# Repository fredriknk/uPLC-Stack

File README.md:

# uPLC - Miniaturized Distributed Monitoring and Control

Quick note, this is then panelization repo, head for the individual repos to get design files.

### PcbWay Sponsorship

Thanks so much to [PCBWay](https://www.pcbway.com/) for sponsoring my first assembly run for this project, they deliver awesome quality assembly service as always with 6 perfectly soldered dual sided prototypes delivered at my door in less than 2 weeks from ordering. All components perfectly placed and good quality 4 layer pcb's. I love the look and legebility of the 0.9mm inverted silkscreen texts. They even pointed out some reccomended component replacements due to NRND bom items. So Look at this beautiful trio of boards ready for automating every dumb device in my house. 

ESP-Home code examples are comming soon.

The uPLC (micro Programmable Logic Controller) is a compact (22x32mm) I/O controller powered by the ESP32, designed to automate various tasks around you. So far, three versions have been developed. All versions are generally 24V-tolerant for digital I/O, except for the analog inputs, and feature a wide-range 3.8-24V buck regulator for power input.

The primary purpose of the uPLC is to "smartify" devices by integrating them with [ESPHome](https://esphome.io/). But it can also function as a direct, point-to-point PLC, using **ESP-NOW** for wireless communication, replacing traditional wired connections at a cost of latency. 

## Available Versions:
- **[uPLC-Digital](https://github.com/fredriknk/uPLC-digital):** High-speed digital I/O
- **[uPLC-Relay](https://github.com/fredriknk/uPLC-relay):** Relays and digital I/O
- **[uPLC-Analog](https://github.com/fredriknk/uPLC-Analog):** ADC and DAC

### Coming Soon:
- **uPLC-COMM:** For sensor connections- SPI, I2C, SDI12 support
- **uPLC-4_20:** Current loop for industrial sensors
- **uPLC-TBD:** If you have a good idea give me a message or issue 

## Specifications

| **Parameter**   | **Description**                                                     |
|-----------------|---------------------------------------------------------------------|
| **Input Voltage** | 3.8-24V                                                           |
| **Current Consumption**  | TBD: WiFi Active: ##mA, Radio Off: ##mA, Deep Sleep: ##uA  |  
| **Communication** | 2.4GHz Wi-Fi, UART (TTL level)                                    |
| **Baud Rate**    | 115200                                                             |
| **PCB Size**     | 22 x 31.1 mm                                                       |
| **PCB Material** | 1.6mm FR4, HASL lead-free, 4-layer                                 |
| **Case Size**    | X x X x X mm (TBD)                                                 |

## uPLC-Stack:
To facilitate manufacturing and development, I've created a panelized version using **KiKit** scripting. The uPLC-Stack includes two units of each version, making it easier to assemble and test multiple variants in one go. Im planning on

### Running the Panelization Script:
To use the panelization script, clone all the uPLC repositories and organize them in a directory one level back from the uPLC-Stack folder. This allows the KiKit script to automatically pull in all required files for panelizing.

### Stack Images

- **Perspective View**  

- **Top View**  

- **Side View**  

- **Bottom View**

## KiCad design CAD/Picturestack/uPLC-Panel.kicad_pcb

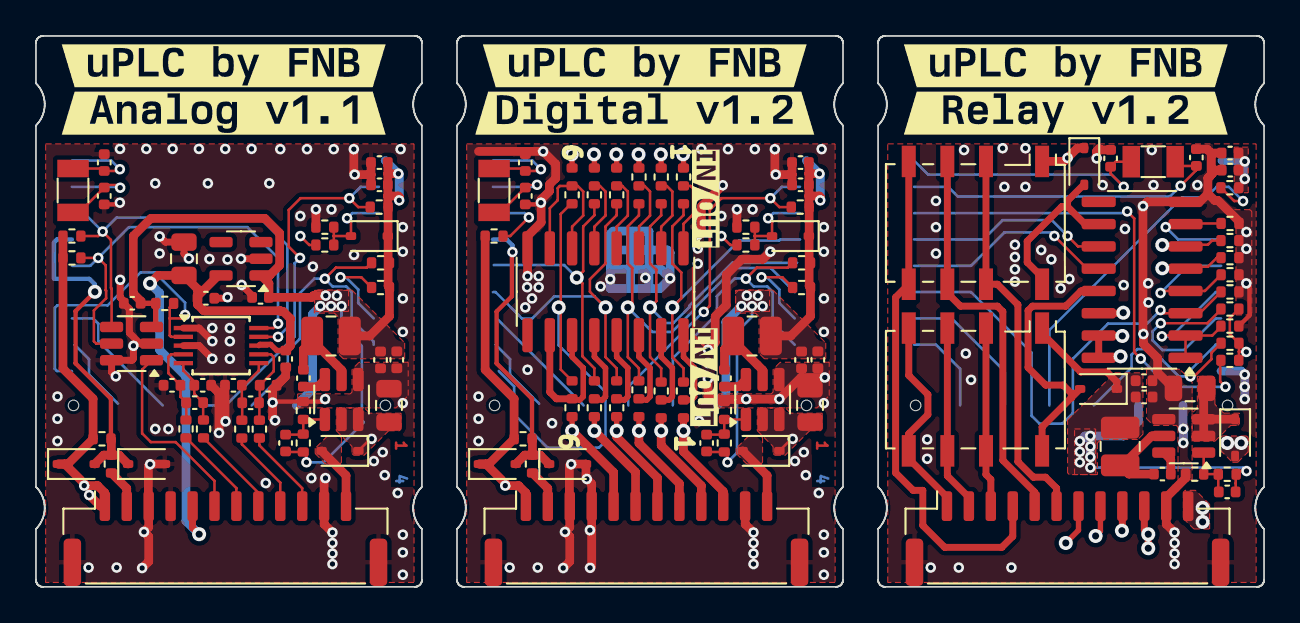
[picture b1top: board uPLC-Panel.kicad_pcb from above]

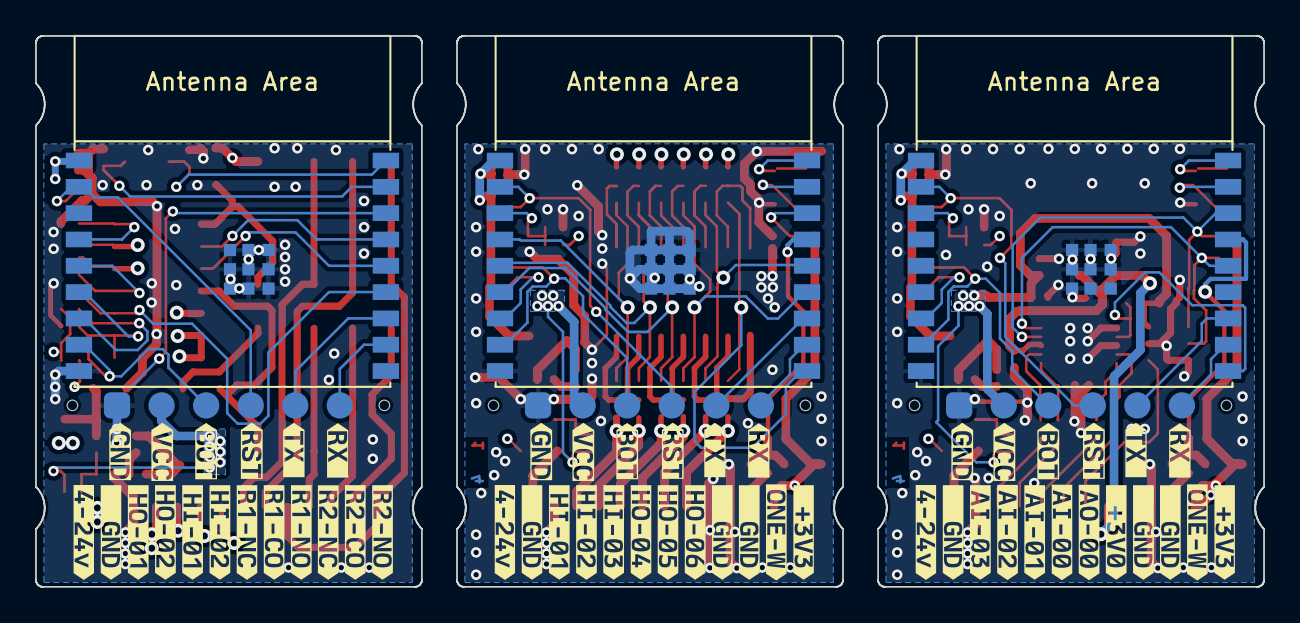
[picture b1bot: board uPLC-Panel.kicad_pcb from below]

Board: 4 copper layers, 70.0 x 31.4 mm, 186 parts (60 on the bottom side), 105 nets.

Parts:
C1.0, C1.1, C1.2, C4.0, C4.1, C4.2: 20pf; C_0402_1005Metric
C2.0, C2.1, C2.2, C3.0, C3.1, C3.2, C6.0, C9.0, C9.1, C9.2, C10.0, C13.0, C14.0, C15.0, C16.0, C17.0, C18.0, C19.0, C20.0: 0.1uF; C_0402_1005Metric
C5.0, C5.1, C5.2, C7.0: 10uF; C_0805_2012Metric
C8.0, C8.1, C8.2, C11.0, C11.1, C11.2, C12.0, C12.1, C12.2: 22uf; C_0402_1005Metric
D1.0, D1.1, D1.2, D2.0, D2.1, D2.2, D3.0, D3.1, D4.0, D4.1, D4.2: 1N5819WS; D_SOD-323
J1.0, J1.1, J1.2: Conn_01x06_Pin; TestPoint_Pad_1.0x1.0mm_6pad
J2.0, J2.1, J2.2: SM12B-GHS-TB(LF)(SN); JST_GH_SM12B-GHS-TB_1x12-1MP_P1.25mm_Horizontal
JP1.1, JP2.1, JP3.1, JP4.1, JP5.1, JP6.1, JP7.1, JP8.1, JP9.1, JP10.1, JP11.1, JP12.1: 0R; SolderJumper-3_P1.3mm_BridgedSMD12_0402
K1.2, K2.2: G6K-2F-Y; Relay_DPDT_Omron_G6K-2F-Y
L1.0, L1.1, L1.2: 4.7uH; L_1008_2520Metric
R1.0, R1.1, R1.2, R2.0, R2.1, R2.2, R3.0, R3.1, R4.0, R4.1, R4.2, R5.0, R5.1, R5.2, R6.0, R6.1, R7.2, R8.2, R9.2, R10.2, R11.2, R12.0, R12.2, R16.0: 10K; R_0402_1005Metric
R7.0, R7.1: 309k; R_0402_1005Metric
R8.0, R9.0, R10.0, R11.0: 499R; R_0402_1005Metric
R13.0, R13.1: 100R; R_0402_1005Metric
R14.0, R14.1, R14.2: 182k; R_0402_1005Metric
R15.0, R15.1, R15.2: 62k; R_0402_1005Metric
U1.0, U1.1, U1.2: AP63201WU; TSOT-23-6
U2.0: ADS1115IDGS; TSSOP-10_3x3mm_P0.5mm
U2.1, U2.2: TBD62003AFWG; SOIC-16_3.9x9.9mm_P1.27mm
U3.0, U3.1, U3.2: ESP32-C3-WROOM-02
U4.0: LP5907MFX-3.0; SOT-23-5
U5.0: MCP4725xxx-xCH; SOT-23-6
Y1.0, Y1.1, Y1.2: 32.768khz 3215 12.5pf; Crystal_SMD_3215-2Pin_3.2x1.5mm
kibuzzard-65D6FF37.2: G***; kibuzzard-65D6FF37
kibuzzard-65D8B0E2.1: G***; kibuzzard-65D8B0E2
kibuzzard-65D8B0ED.1: G***; kibuzzard-65D8B0ED
kibuzzard-65D8B0F8.1: G***; kibuzzard-65D8B0F8
kibuzzard-65D8B10C.1: G***; kibuzzard-65D8B10C
kibuzzard-65D8B28C.1: G***; kibuzzard-65D8B28C
kibuzzard-65D8B104.1: G***; kibuzzard-65D8B104
kibuzzard-65D8B121.1: G***; kibuzzard-65D8B121
kibuzzard-65D8B297.1: G***; kibuzzard-65D8B297
kibuzzard-65D8B343.1: G***; kibuzzard-65D8B343
kibuzzard-65D74DE1.0, kibuzzard-65D74DE1.0#2, kibuzzard-65D74DE1.1: G***; kibuzzard-65D74DE1
kibuzzard-65D74DEE.0, kibuzzard-65D74DEE.1: G***; kibuzzard-65D74DEE
kibuzzard-65D74DFB.0, kibuzzard-65D74DFB.1: G***; kibuzzard-65D74DFB
kibuzzard-65D361A7.2: G***; kibuzzard-65D361A7
kibuzzard-65D361B0.2: G***; kibuzzard-65D361B0
kibuzzard-65D361D3.2: G***; kibuzzard-65D361D3
kibuzzard-65D361E1.2: G***; kibuzzard-65D361E1
kibuzzard-65D361E9.2: G***; kibuzzard-65D361E9
kibuzzard-65D361F2.2: G***; kibuzzard-65D361F2
kibuzzard-65D361FD.2: G***; kibuzzard-65D361FD
kibuzzard-65D460A0.0, kibuzzard-65D460A0.1, kibuzzard-65D460A0.2: G***; kibuzzard-65D460A0
kibuzzard-65D3616E.0, kibuzzard-65D3616E.1, kibuzzard-65D3616E.2: G***; kibuzzard-65D3616E
kibuzzard-65D3619D.2: G***; kibuzzard-65D3619D
kibuzzard-65D3620E.2: G***; kibuzzard-65D3620E
kibuzzard-65D7176D.0, kibuzzard-65D7176D.1, kibuzzard-65D7176D.2: G***; kibuzzard-65D7176D
kibuzzard-65D7177B.0, kibuzzard-65D7177B.1, kibuzzard-65D7177B.2: G***; kibuzzard-65D7177B
kibuzzard-65D36177.0, kibuzzard-65D36177.1, kibuzzard-65D36177.2: G***; kibuzzard-65D36177
kibuzzard-65D36206.2: G***; kibuzzard-65D36206
kibuzzard-65D46022.0, kibuzzard-65D46022.1, kibuzzard-65D46022.2: G***; kibuzzard-65D46022
kibuzzard-65D46066.0, kibuzzard-65D46066.1, kibuzzard-65D46066.2: G***; kibuzzard-65D46066
kibuzzard-65D49092.0, kibuzzard-65D49092.1, kibuzzard-65D49092.2: G***; kibuzzard-65D49092
kibuzzard-65D71774.0, kibuzzard-65D71774.1, kibuzzard-65D71774.2: G***; kibuzzard-65D71774
kibuzzard-65DC95DA.0: G***; kibuzzard-65DC95DA
kibuzzard-65DC95E5.0: G***; kibuzzard-65DC95E5
kibuzzard-65DC95EF.0: G***; kibuzzard-65DC95EF
kibuzzard-65DC95F6.0: G***; kibuzzard-65DC95F6
kibuzzard-65DC961D.0: G***; kibuzzard-65DC961D
kibuzzard-65DC9610.0: G***; kibuzzard-65DC9610
kibuzzard-65DCA831.1: G***; kibuzzard-65DCA831
kibuzzard-65DCE4DE.0: G***; kibuzzard-65DCE4DE

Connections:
+3.3V.0: C3.0.1, C8.0.1, C9.0.1, C10.0.1, C11.0.1, C12.0.1, C14.0.1, D1.0.1 (K), D3.0.1 (K), J1.0.2, J2.0.1, L1.0.2, R1.0.1, R2.0.1, R4.0.2, R5.0.2, R6.0.1, R12.0.2, R14.0.2, R16.0.2, U3.0.1 (3V3), U4.0.1 (IN), U5.0.3 (VDD)
+3.3V.1: C3.1.1, C8.1.1, C9.1.1, C11.1.1, C12.1.1, D1.1.1 (K), D3.1.1 (K), J1.1.2, J2.1.1, L1.1.2, R1.1.1, R2.1.1, R4.1.2, R5.1.2, R6.1.1, R14.1.2, U3.1.1 (3V3)
+3.3V.2: C3.2.1, C8.2.1, C9.2.1, C11.2.1, C12.2.1, D1.2.1 (K), D2.2.1 (K), J1.2.2, K1.2.1, K2.2.1, L1.2.2, R1.2.1, R2.2.1, R4.2.2, R5.2.2, R14.2.2, U3.2.1 (3V3)
+3V0.0: C6.0.1, C7.0.1, C13.0.1, J2.0.5, U2.0.8 (VDD), U4.0.5 (OUT)
+VDC.0: D4.0.2 (A), J2.0.12
+VDC.1: D4.1.2 (A), J2.1.12
+VDC.2: D4.2.2 (A), J2.2.12
/FB.0: C9.0.2, R14.0.1, R15.0.2, U1.0.1 (FB)
/FB.1: C9.1.2, R14.1.1, R15.1.2, U1.1.1 (FB)
/FB.2: C9.2.2, R14.2.1, R15.2.2, U1.2.1 (FB)
/I1.1: JP1.1.2 (C), U2.1.1 (I1)
/I2.1: JP3.1.2 (C), U2.1.2 (I2)
/I3.1: JP5.1.2 (C), U2.1.3 (I3)
/I4.1: JP7.1.2 (C), U2.1.4 (I4)
/I5.1: JP9.1.2 (C), U2.1.5 (I5)
/I6.1: JP11.1.2 (C), U2.1.6 (I6), U2.1.7 (I7)
/O1.1: JP2.1.2 (C), U2.1.16 (O1)
/O2.1: JP4.1.2 (C), U2.1.15 (O2)
/O3.1: JP6.1.2 (C), U2.1.14 (O3)
/O4.1: JP8.1.2 (C), U2.1.13 (O4)
/O5.1: JP10.1.2 (C), U2.1.12 (O5)
/O6.1: JP12.1.2 (C), U2.1.10 (O7), U2.1.11 (O6)
/SW.0: C2.0.1, L1.0.1, U1.0.5 (SW)
/SW.1: C2.1.1, L1.1.1, U1.1.5 (SW)
/SW.2: C2.2.1, L1.2.1, U1.2.5 (SW)
/VIN_P.0: C5.0.1, D4.0.1 (K), R7.0.1, U1.0.2 (EN), U1.0.3 (IN)
/VIN_P.1: C5.1.1, D4.1.1 (K), R7.1.1, U1.1.2 (EN), U1.1.3 (IN)
/VIN_P.2: C5.2.1, D4.2.1 (K), U1.2.2 (EN), U1.2.3 (IN)
ADC.0: D3.0.2 (A), R3.0.1, R7.0.2, U3.0.3 (GPIO4/ADC1_CH4)
ADC.1: D3.1.2 (A), R3.1.1, R7.1.2, U3.1.3 (GPIO4/ADC1_CH4)
ADC_DRDY.0: R12.0.1, U2.0.2 (ALERT/RDY), U3.0.10 (GPIO10)
AIN0.0: J2.0.7, R8.0.2
AIN1.0: J2.0.8, R9.0.2
AIN2.0: J2.0.9, R10.0.2
AIN3.0: J2.0.10, R11.0.2
AOUT0.0: J2.0.6, U5.0.1 (VOUT)
BOOT.0: J1.0.3, R2.0.2, U3.0.8 (GPIO9)
BOOT.1: J1.1.3, R2.1.2, U3.1.8 (GPIO9)
BOOT.2: J1.2.3, R2.2.2, U3.2.8 (GPIO9)
GND.0: C1.0.1, C3.0.2, C4.0.2, C5.0.2, C6.0.2, C7.0.2, C8.0.2, C10.0.2, C11.0.2, C12.0.2, C13.0.2, C14.0.2, C15.0.1, C16.0.1, C17.0.1, C18.0.1, D2.0.2 (A), J1.0.1, J2.0.3, J2.0.4, J2.0.11, J2.0.MP (Pin_13), R3.0.2, R15.0.1, U1.0.4 (GND), U2.0.1 (ADDR), U2.0.3 (GND), U3.0.9 (GND), U3.0.19 (GND), U4.0.2 (GND), U5.0.2 (VSS), U5.0.6 (A0)
GND.1: C1.1.1, C3.1.2, C4.1.2, C5.1.2, C8.1.2, C11.1.2, C12.1.2, D2.1.2 (A), J1.1.1, J2.1.3, J2.1.4, J2.1.11, J2.1.MP (Pin_13), R3.1.2, R15.1.1, U1.1.4 (GND), U2.1.8 (GND), U3.1.9 (GND), U3.1.19 (GND)
GND.2: C1.2.1, C3.2.2, C4.2.2, C5.2.2, C8.2.2, C11.2.2, C12.2.2, J1.2.1, J2.2.11, J2.2.MP (Pin_13), R7.2.2, R8.2.2, R9.2.2, R10.2.2, R11.2.2, R12.2.2, R15.2.1, U1.2.4 (GND), U2.2.8 (GND), U3.2.9 (GND), U3.2.19 (GND)
H1.1: J2.1.10, JP1.1.1 (A), JP2.1.3 (B)
H2.1: J2.1.9, JP3.1.1 (A), JP4.1.3 (B)
H3.1: J2.1.8, JP5.1.1 (A), JP6.1.3 (B)
H4.1: J2.1.7, JP7.1.3 (B), JP8.1.1 (A)
H5.1: J2.1.6, JP9.1.3 (B), JP10.1.1 (A)
H6.1: J2.1.5, JP11.1.3 (B), JP12.1.1 (A)
HI1.2: J2.2.8, R12.2.1, U2.2.5 (I5)
HI2.2: J2.2.7, R11.2.1, U2.2.6 (I6)
HO1.2: J2.2.10, U2.2.15 (O2), U2.2.16 (O1)
HO2.2: J2.2.9, U2.2.14 (O3)
L1.1: JP1.1.3 (B), JP2.1.1 (A), U3.1.4 (GPIO5/ADC2_CH0)
L2.1: JP3.1.3 (B), JP4.1.1 (A), U3.1.5 (GPIO6)
L3.1: JP5.1.3 (B), JP6.1.1 (A), U3.1.6 (GPIO7)
L4.1: JP7.1.1 (A), JP8.1.3 (B), U3.1.13 (GPIO18/USB_D-)
L5.1: JP9.1.1 (A), JP10.1.3 (B), U3.1.14 (GPIO19/USB_D+)
L6.1: JP11.1.1 (A), JP12.1.3 (B), U3.1.10 (GPIO10)
LI3.2: R8.2.1, U2.2.3 (I3), U3.2.13 (GPIO18/USB_D-)
LI4.2: R9.2.1, U2.2.4 (I4), U3.2.5 (GPIO6)
LI5.2: R10.2.1, U2.2.7 (I7), U3.2.4 (GPIO5/ADC2_CH0)
LI12.2: R7.2.1, U2.2.1 (I1), U2.2.2 (I2), U3.2.6 (GPIO7)
LO6.2: U2.2.12 (O5), U3.2.14 (GPIO19/USB_D+)
LO7.2: U2.2.11 (O6), U3.2.15 (GPIO3/ADC1_CH3)
unnamed: C2.0.2, U1.0.6 (BST)
unnamed: C2.1.2, U1.1.6 (BST)
unnamed: C2.2.2, U1.2.6 (BST)
unnamed: C15.0.2, C19.0.1, R8.0.1, U2.0.4 (AIN0)
unnamed: C16.0.2, C19.0.2, R9.0.1, U2.0.5 (AIN1)
unnamed: C17.0.2, C20.0.1, R10.0.1, U2.0.6 (AIN2)
unnamed: C18.0.2, C20.0.2, R11.0.1, U2.0.7 (AIN3)
unnamed: C1.0.2, U3.0.18 (GPIO0/ADC1_CH0/XTAL_32K_P), Y1.0.2
unnamed: C1.1.2, U3.1.18 (GPIO0/ADC1_CH0/XTAL_32K_P), Y1.1.2
unnamed: C1.2.2, U3.2.18 (GPIO0/ADC1_CH0/XTAL_32K_P), Y1.2.2
unnamed: C4.0.1, U3.0.17 (GPIO1/ADC1_CH1/XTAL_32K_N), Y1.0.1
unnamed: C4.1.1, U3.1.17 (GPIO1/ADC1_CH1/XTAL_32K_N), Y1.1.1
unnamed: C4.2.1, U3.2.17 (GPIO1/ADC1_CH1/XTAL_32K_N), Y1.2.1
unnamed: R5.1.1, U3.1.16 (GPIO2/ADC1_CH2)
unnamed: R5.2.1, U3.2.16 (GPIO2/ADC1_CH2)
unnamed: R4.0.1, U3.0.7 (GPIO8)
unnamed: R4.1.1, U3.1.7 (GPIO8)
unnamed: R4.2.1, U3.2.7 (GPIO8)
ONEWIRE.0: D1.0.2 (A), D2.0.1 (K), R6.0.2, R13.0.2, U3.0.15 (GPIO3/ADC1_CH3)
ONEWIRE.1: D1.1.2 (A), D2.1.1 (K), R6.1.2, R13.1.2, U3.1.15 (GPIO3/ADC1_CH3)
ONEWIRE_OUT.0: J2.0.2, R13.0.1
ONEWIRE_OUT.1: J2.1.2, R13.1.1
R1CO.2: J2.2.5, K1.2.3, K1.2.6
R1NC.2: J2.2.6, K1.2.2, K1.2.7
R1NO.2: J2.2.4, K1.2.4, K1.2.5
R2CO.2: J2.2.2, K2.2.3, K2.2.6
R2NC.2: J2.2.3, K2.2.2, K2.2.7
R2NO.2: J2.2.1, K2.2.4, K2.2.5
RO1.2: D1.2.2 (A), K1.2.8, U2.2.10 (O7)
RO2.2: D2.2.2 (A), K2.2.8, U2.2.13 (O4)
RST.0: J1.0.4, R1.0.2, U3.0.2 (EN/CHIP_PU)
RST.1: J1.1.4, R1.1.2, U3.1.2 (EN/CHIP_PU)
RST.2: J1.2.4, R1.2.2, U3.2.2 (EN/CHIP_PU)
RX.0: J1.0.6, U3.0.11 (GPIO20/U0RXD)
RX.1: J1.1.6, U3.1.11 (GPIO20/U0RXD)
RX.2: J1.2.6, U3.2.11 (GPIO20/U0RXD)
SCL.0: R16.0.1, U2.0.10 (SCL), U3.0.14 (GPIO19/USB_D+), U5.0.5 (SCL)
SDA.0: R5.0.1, U2.0.9 (SDA), U3.0.16 (GPIO2/ADC1_CH2), U5.0.4 (SDA)
TX.0: J1.0.5, U3.0.12 (GPIO21/U0TXD)
TX.1: J1.1.5, U3.1.12 (GPIO21/U0TXD)
TX.2: J1.2.5, U3.2.12 (GPIO21/U0TXD)

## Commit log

2024-10-14 Readme update and picture stack
2024-10-14 Readme fixes
2025-04-09 Feat: real pictures
2025-04-09 Feat:Bottom real pictures
2025-04-09 Feat: Prodrun
